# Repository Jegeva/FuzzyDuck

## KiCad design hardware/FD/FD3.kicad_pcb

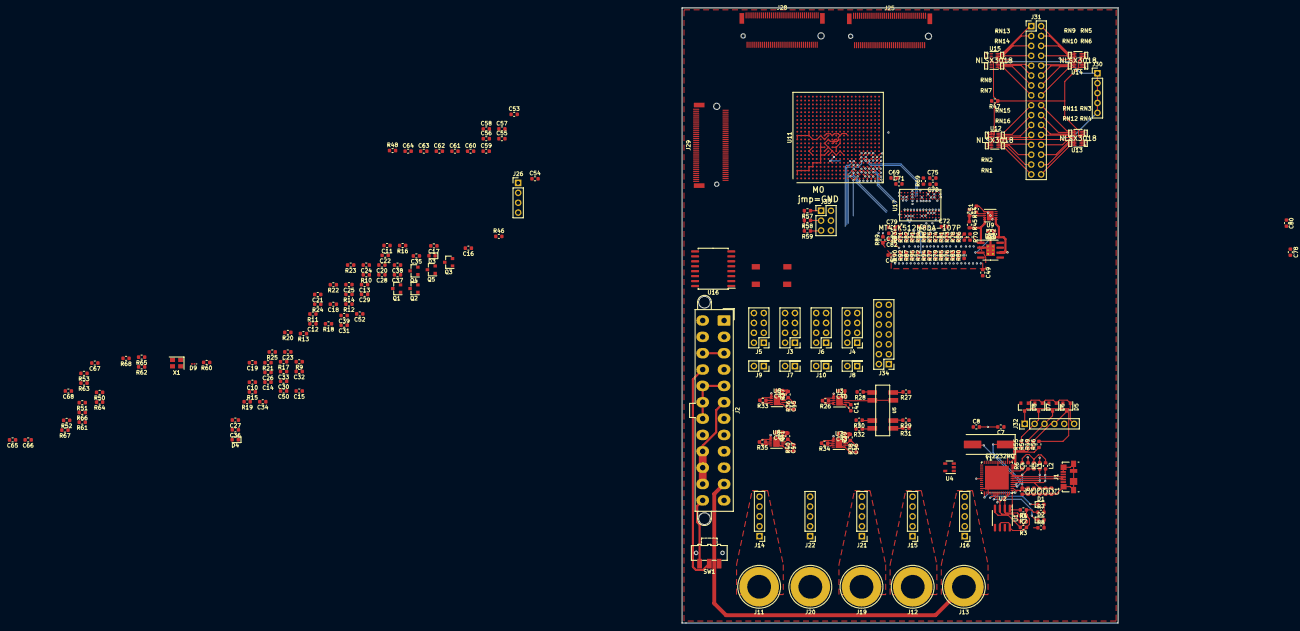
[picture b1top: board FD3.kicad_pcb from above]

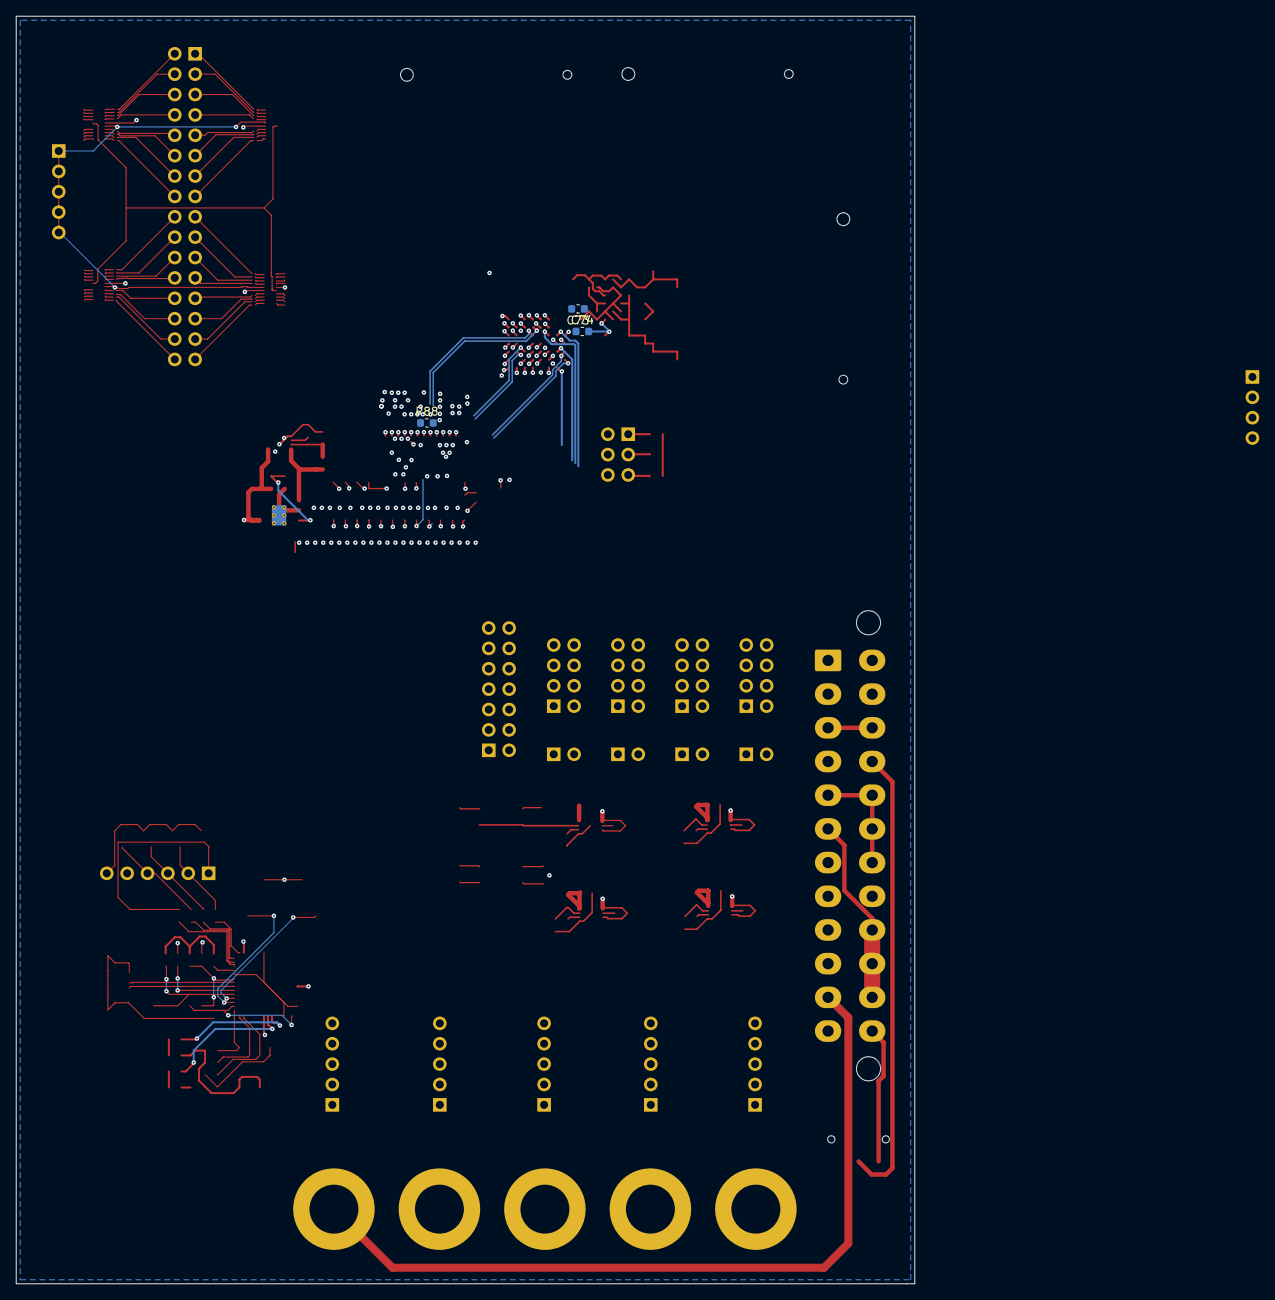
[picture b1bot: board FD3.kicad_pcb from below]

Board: 6 copper layers, 112.0 x 158.0 mm, 259 parts (3 on the bottom side), 413 nets.

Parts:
C1, C4: 4.7uF TA; C_0603_1608Metric
C2, C5, C66, C67, C68, C70, C71, C72, C73, C75, C79, C80, C82: 100nF; C_0603_1608Metric
C3, C6, C65, C69, C76, C77: 10nF; C_0603_1608Metric
C7, C8: 20pF; C_0603_1608Metric
C9, C10, C11, C12, C13, C14, C15, C16, C17, C18, C19, C20, C21: 4.7uF; C_0603_1608Metric
C22, C27, C40, C42, C43, C44, C48, C50: 100uF; C_0603_1608Metric
C23, C24, C25, C26, C28, C29, C30, C31, C32, C33, C34, C35: 0.47uF; C_0603_1608Metric
C36, C37, C38, C39: 0.1uF; C_0603_1608Metric
C41, C45, C46, C47, C51: 5.6nF; C_0603_1608Metric
C49, C52, C74, C78: 10uF; C_0603_1608Metric
C53, C54, C55, C56, C57, C58, C59, C60, C61, C62, C63, C64: 200nF; C_0603_1608Metric
D1, D2: LED_Small; LED_0603_1608Metric
D3, D4: LED; LED_0603_1608Metric
D5, D6, D7, D8: MMSZ4678-TPMSCT-ND‎; D_SOT-23_ANK
D9: LED_Small; LED_0201_0603Metric
J1: USB_B_Micro; USB_Micro-B_Molex_47346-0001
J2: ATX-24; Molex_Mini-Fit_Jr_5566-24A2_2x12_P4.20mm_Vertical
J3, J4, J5, J6: Conn_01x05; PinHeader_2x04_P2.54mm_Vertical
J7, J8, J9, J10: Conn_01x02_Male; PinHeader_2x01_P2.54mm_Vertical
J11, J12, J13, J19, J20: Conn_01x01_Male; Banana_Jack_1Pin
J14, J15, J16, J21, J22: Conn_01x05; PinHeader_1x05_P2.54mm_Vertical
J25, J28, J29: M.2_Socket_M; m.2
J26: Conn_01x06_Male; PinHeader_1x04_P2.54mm_Vertical
J30: Conn_01x05_Male; PinHeader_1x05_P2.54mm_Vertical
J31: Conn_02x16_Counter_Clockwise; PinHeader_2x16_P2.54mm_Vertical
J32: Conn_01x06_Male; PinHeader_1x06_P2.54mm_Vertical
J33: Conn_02x03_Counter_Clockwise; PinHeader_2x03_P2.54mm_Vertical
J34: Conn_02x07_Counter_Clockwise; PinHeader_2x07_P2.54mm_Vertical
L1, L2: 600R/100MHz; R_0603_1608Metric
Q1, Q2, Q3, Q4, Q5: DMG2301L; SOT-23
R1, R2, R3: 10k; R_0603_1608Metric
R4: 2.2k; R_0603_1608Metric
R5: 12k; R_0603_1608Metric
R6, R52, R53, R57, R58, R59: 1k; R_0603_1608Metric
R7, R8, R12, R17: 220; R_0603_1608Metric
R9, R10, R11, R13, R14, R15, R16, R18, R19, R20, R21, R22, R23, R24, R25, R26, R33, R34, R35, R42, R43: 47k; R_0603_1608Metric
R27, R36: 4.53k; R_0603_1608Metric
R28, R37: 1.13k; R_0603_1608Metric
R29, R38: 4.99k; R_0603_1608Metric
R30, R39: 2.49k; R_0603_1608Metric
R31, R40: 2.87k; R_0603_1608Metric
R32, R41: 3.57k; R_0603_1608Metric
R44, R47, R50, R51: 4.7k; R_0603_1608Metric
R45: 3.3k; R_0603_1608Metric
R46: 49.9; R_0603_1608Metric
R48, R49, R54, R55, R56, R60, R61: 100; R_0603_1608Metric
R62: 200; R_0603_1608Metric
R63, R64: 1.8k; R_0603_1608Metric
R65, R66, R67, R68: 50; R_0603_1608Metric
R69: 240; R_0603_1608Metric
R70, R93: 34; R_0603_1608Metric
R71, R72, R73, R74, R75, R76, R77, R78, R79, R80, R81, R82, R83, R84, R85, R86, R87, R89, R90, R91, R92, R94, R95, R96: 40; R_0603_1608Metric
R88: 68; R_0603_1608Metric
RN1, RN2, RN3, RN4, RN5, RN6, RN7, RN8, RN9, RN10, RN11, RN12, RN13, RN14, RN15, RN16: 1k x4; Resistor_Array_4x0503
SW1: SW_SPDT; SW_SPDT_CK-JS102011SAQN
SW2: SW_SPST; FSM4JSMATR
U1: 93CxxC; SOIC-8_3.9x4.9mm_P1.27mm
U2: FT2232HQ; VQFN-56-ftdi2232h-56q
U3, U6, U7, U8, U9: NCP59744-DFN10; DFN-10-1EP_3x3mm_P0.5mm_EP1.7x2.5mm
U4: 74LX1G00; SOT-23-5
U5: SWITCH_DP3T; JS203011SCQN
U10: AP2303; SOIC-8-1EP_3.9x4.9mm_P1.27mm_EP2.29x3mm_ThermalVias
U11: XC7A100T-FGG484; Xilinx_FGG484.p2d
U12, U13, U14, U15: NLSX3018; ON_Semiconductor-517AK-01-11_2006-O-MFG
U16: MT25Q128-8-ESF_SO16; SOIC-16W_7.5x10.3mm_P1.27mm
U17: MT41K512M8DA-107P; Micron-DA-0-0-0
X1: ASTMLPE-18-100.000MHZ-LJ-E-T; Oscillator_SMD_Abracon_ASE-4Pin_3.2x2.5mm
Y1: 12 MHz; Crystal_SMD_HC49-SD

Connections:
+3.3V: C27.2, J2.1 (+3.3V), J2.2 (+3.3V), J2.12 (+3.3V), J2.13 (+3.3V), J3.2, J4.2, J5.2, J6.2, J19.1, J21.1, J21.2, J21.3, J21.4, J21.5, J25.12 (3.3V), J28.12 (3.3V), J29.2 (3.3V), J29.4 (3.3V), J29.12 (3.3V), J29.14 (3.3V), J29.16 (3.3V), J29.18 (3.3V), J29.70 (3.3V), J29.72 (3.3V), J29.74 (3.3V), L1.1, L2.1, R1.1, R2.1, R3.1, R6.2, R7.1, R8.1, U1.6 (ORG), U1.8 (VCC), U2.16 (VCCIO), U2.36 (VCCIO), U2.44 (VREGIN), U2.50 (VCCIO)
+5V: C22.2, J2.4 (+5V), J2.6 (+5V), J2.21 (+5V), J2.22 (+5V), J2.23 (+5V), J12.1, J15.1, J15.2, J15.3, J15.4, J15.5, R26.2, R33.2, R34.2, R35.2, R43.1, U3.1 (IN), U3.2 (IN), U3.4 (BIAS), U4.5 (VCC), U6.1 (IN), U6.2 (IN), U6.4 (BIAS), U7.1 (IN), U7.2 (IN), U7.4 (BIAS), U8.1 (IN), U8.2 (IN), U8.4 (BIAS), U9.1 (IN), U9.2 (IN), U9.4 (BIAS), U10.6 (VCNTL)
+12V: J2.10 (+12V), J2.11 (+12V), J13.1, J16.1, J16.2, J16.3, J16.4, J16.5
-12V: J2.14 (-12V), J11.1, J14.1, J14.2, J14.3, J14.4, J14.5
/fgpa-logic/m0: J33.1, R57.1, U11.U11 (M0_0)
/fgpa-logic/m1: J33.3, R58.1, U11.U10 (M1_0)
/fgpa-logic/m2: J33.5, R59.1, U11.U9 (M2_0)
/fpga-io/b15_1_N: J25.47 (FDEXP_D1_N), U11.G13 (IO_L1N_T0_AD0N_15)
/fpga-io/b15_1_P: J25.49 (FDEXP_D1_P), U11.H13 (IO_L1P_T0_AD0P_15)
/fpga-io/b15_2_N: J25.41 (FDEXP_D2_N), U11.G16 (IO_L2N_T0_AD8N_15)
/fpga-io/b15_2_P: J25.43 (FDEXP_D2_P), U11.G15 (IO_L2P_T0_AD8P_15)
/fpga-io/b15_3_N: J25.53 (FDEXP_D3_N), U11.H14 (IO_L3N_T0_DQS_AD1N_15)
/fpga-io/b15_3_P: J25.55 (FDEXP_D3_P), U11.J14 (IO_L3P_T0_DQS_AD1P_15)
/fpga-io/b15_4_N: J25.52 (FDEXP_D4_N), U11.G18 (IO_L4N_T0_15)
/fpga-io/b15_4_P: J25.50 (FDEXP_D4_P), U11.G17 (IO_L4P_T0_15)
/fpga-io/b15_5_N: J25.37 (FDEXP_D5_N), U11.H15 (IO_L5N_T0_AD9N_15)
/fpga-io/b15_5_P: J25.54 (FDEXP_D5_P), U11.J15 (IO_L5P_T0_AD9P_15)
/fpga-io/b15_7_N: J25.29 (FDEXP_D7_N), U11.H22 (IO_L7N_T1_AD2N_15)
/fpga-io/b15_7_P: J25.31 (FDEXP_D7_P), U11.J22 (IO_L7P_T1_AD2P_15)
/fpga-io/b15_8_N: J25.23 (FDEXP_D8_N), U11.G20 (IO_L8N_T1_AD10N_15)
/fpga-io/b15_8_P: J25.25 (FDEXP_D8_P), U11.H20 (IO_L8P_T1_AD10P_15)
/fpga-io/b15_9_N: J25.17 (FDEXP_D9_N), U11.K22 (IO_L9N_T1_DQS_AD3N_15)
/fpga-io/b15_9_P: J25.19 (FDEXP_D9_P), U11.K21 (IO_L9P_T1_DQS_AD3P_15)
/fpga-io/b15_10_N: J25.11 (FDEXP_D10_N), U11.L21 (IO_L10N_T1_AD11N_15)
/fpga-io/b15_10_P: J25.13 (FDEXP_D10_P), U11.M21 (IO_L10P_T1_AD11P_15)
/fpga-io/b15_11_N: J25.5 (FDEXP_D11_N), U11.J21 (IO_L11N_T1_SRCC_15)
/fpga-io/b15_11_P: J25.7 (FDEXP_D11_P), U11.J20 (IO_L11P_T1_SRCC_15)
/fpga-io/b15_12_N: J25.18 (FDEXP_D12_N), U11.H19 (IO_L12N_T1_MRCC_15)
/fpga-io/b15_12_P: J25.16 (FDEXP_D12_P), U11.J19 (IO_L12P_T1_MRCC_15)
/fpga-io/b15_13_N: J25.4 (FDEXP_D13_N), U11.K19 (IO_L13N_T2_MRCC_15)
/fpga-io/b15_13_P: J25.2 (FDEXP_D13_P), U11.K18 (IO_L13P_T2_MRCC_15)
/fpga-io/b15_14_N: J25.74 (FDEXP_D14_N), U11.L20 (IO_L14N_T2_SRCC_15)
/fpga-io/b15_14_P: J25.72 (FDEXP_D14_P), U11.L19 (IO_L14P_T2_SRCC_15)
/fpga-io/b15_15_N: J25.3 (FDEXP_D15_N), U11.M22 (IO_L15N_T2_DQS_ADV_B_15)
/fpga-io/b15_15_P: J25.1 (FDEXP_D15_P), U11.N22 (IO_L15P_T2_DQS_15)
/fpga-io/b15_16_N: J25.15 (FDEXP_D16_N), U11.L18 (IO_L16N_T2_A27_15)
/fpga-io/b15_16_P: J25.9 (FDEXP_D16_P), U11.M18 (IO_L16P_T2_A28_15)
/fpga-io/b15_17_N: J25.27 (FDEXP_D17_N), U11.N19 (IO_L17N_T2_A25_15)
/fpga-io/b15_17_P: J25.21 (FDEXP_D17_P), U11.N18 (IO_L17P_T2_A26_15)
/fpga-io/b15_18_N: J25.39 (FDEXP_D18_N), U11.M20 (IO_L18N_T2_A23_15)
/fpga-io/b15_18_P: J25.33 (FDEXP_D18_P), U11.N20 (IO_L18P_T2_A24_15)
/fpga-io/b15_20_N: J25.57 (FDEXP_D20_N), U11.L13 (IO_L20N_T3_A19_15)
/fpga-io/b15_20_P: J25.51 (FDEXP_D20_p), U11.M13 (IO_L20P_T3_A20_15)
/fpga-io/b15_21_N: J25.73 (FDEXP_D21_N), U11.J17 (IO_L21N_T3_DQS_A18_15)
/fpga-io/b15_21_P: J25.71 (FDEXP_D21_P), U11.K17 (IO_L21P_T3_DQS_15)
/fpga-io/b15_22_N: J25.69 (FDEXP_D22_N), U11.L15 (IO_L22N_T3_A16_15)
/fpga-io/b15_22_P: J25.68 (FDEXP_D22_P), U11.L14 (IO_L22P_T3_A17_15)
/fpga-io/b15_23_N: J25.10 (FDEXP_D23_N), U11.K16 (IO_L23N_T3_FWE_B_15)
/fpga-io/b15_23_P: J25.75 (FDEXP_D23_P), U11.L16 (IO_L23P_T3_FOE_B_15)
/fpga-io/b16_1_N: J28.47 (FDEXP_D1_N), U11.F14 (IO_L1N_T0_16)
/fpga-io/b16_1_P: J28.49 (FDEXP_D1_P), U11.F13 (IO_L1P_T0_16)
/fpga-io/b16_2_N: J28.41 (FDEXP_D2_N), U11.E17 (IO_L2N_T0_16)
/fpga-io/b16_2_P: J28.43 (FDEXP_D2_P), U11.F16 (IO_L2P_T0_16)
/fpga-io/b16_3_N: J28.53 (FDEXP_D3_N), U11.C15 (IO_L3N_T0_DQS_16)
/fpga-io/b16_3_P: J28.55 (FDEXP_D3_P), U11.C14 (IO_L3P_T0_DQS_16)
/fpga-io/b16_4_N: J28.52 (FDEXP_D4_N), U11.E14 (IO_L4N_T0_16)
/fpga-io/b16_4_P: J28.50 (FDEXP_D4_P), U11.E13 (IO_L4P_T0_16)
/fpga-io/b16_5_N: J28.37 (FDEXP_D5_N), U11.D16 (IO_L5N_T0_16)
/fpga-io/b16_5_P: J28.54 (FDEXP_D5_P), U11.E16 (IO_L5P_T0_16)
/fpga-io/b16_7_N: J28.29 (FDEXP_D7_N), U11.B16 (IO_L7N_T1_16)
/fpga-io/b16_7_P: J28.31 (FDEXP_D7_P), U11.B15 (IO_L7P_T1_16)
/fpga-io/b16_8_N: J28.23 (FDEXP_D8_N), U11.B13 (IO_L8N_T1_16)
/fpga-io/b16_8_P: J28.25 (FDEXP_D8_P), U11.C13 (IO_L8P_T1_16)
/fpga-io/b16_9_N: J28.17 (FDEXP_D9_N), U11.A16 (IO_L9N_T1_DQS_16)
/fpga-io/b16_9_P: J28.19 (FDEXP_D9_P), U11.A15 (IO_L9P_T1_DQS_16)
/fpga-io/b16_10_N: J28.11 (FDEXP_D10_N), U11.A14 (IO_L10N_T1_16)
/fpga-io/b16_10_P: J28.13 (FDEXP_D10_P), U11.A13 (IO_L10P_T1_16)
/fpga-io/b16_11_N: J28.5 (FDEXP_D11_N), U11.B18 (IO_L11N_T1_SRCC_16)
/fpga-io/b16_11_P: J28.7 (FDEXP_D11_P), U11.B17 (IO_L11P_T1_SRCC_16)
/fpga-io/b16_12_N: J28.18 (FDEXP_D12_N), U11.C17 (IO_L12N_T1_MRCC_16)
/fpga-io/b16_12_P: J28.16 (FDEXP_D12_P), U11.D17 (IO_L12P_T1_MRCC_16)
/fpga-io/b16_13_N: J28.4 (FDEXP_D13_N), U11.C19 (IO_L13N_T2_MRCC_16)
/fpga-io/b16_13_P: J28.2 (FDEXP_D13_P), U11.C18 (IO_L13P_T2_MRCC_16)
/fpga-io/b16_14_N: J28.74 (FDEXP_D14_N), U11.D19 (IO_L14N_T2_SRCC_16)
/fpga-io/b16_14_P: J28.72 (FDEXP_D14_P), U11.E19 (IO_L14P_T2_SRCC_16)
/fpga-io/b16_15_N: J28.3 (FDEXP_D15_N), U11.E18 (IO_L15N_T2_DQS_16)
/fpga-io/b16_15_P: J28.1 (FDEXP_D15_P), U11.F18 (IO_L15P_T2_DQS_16)
/fpga-io/b16_16_N: J28.15 (FDEXP_D16_N), U11.A20 (IO_L16N_T2_16)
/fpga-io/b16_16_P: J28.9 (FDEXP_D16_P), U11.B20 (IO_L16P_T2_16)
/fpga-io/b16_17_N: J28.27 (FDEXP_D17_N), U11.A19 (IO_L17N_T2_16)
/fpga-io/b16_17_P: J28.21 (FDEXP_D17_P), U11.A18 (IO_L17P_T2_16)
/fpga-io/b16_18_N: J28.39 (FDEXP_D18_N), U11.F20 (IO_L18N_T2_16)
/fpga-io/b16_18_P: J28.33 (FDEXP_D18_P), U11.F19 (IO_L18P_T2_16)
/fpga-io/b16_20_N: J28.57 (FDEXP_D20_N), U11.B22 (IO_L20N_T3_16)
/fpga-io/b16_20_P: J28.51 (FDEXP_D20_p), U11.C22 (IO_L20P_T3_16)
/fpga-io/b16_21_N: J28.73 (FDEXP_D21_N), U11.A21 (IO_L21N_T3_DQS_16)
/fpga-io/b16_21_P: J28.71 (FDEXP_D21_P), U11.B21 (IO_L21P_T3_DQS_16)
/fpga-io/b16_22_N: J28.69 (FDEXP_D22_N), U11.D22 (IO_L22N_T3_16)
/fpga-io/b16_22_P: J28.68 (FDEXP_D22_P), U11.E22 (IO_L22P_T3_16)
/fpga-io/b16_23_N: J28.10 (FDEXP_D23_N), U11.D21 (IO_L23N_T3_16)
/fpga-io/b16_23_P: J28.75 (FDEXP_D23_P), U11.E21 (IO_L23P_T3_16)
/usb-interface/D+: J1.3 (D+), U2.8 (DP)
/usb-interface/D-: J1.2 (D-), U2.7 (DM)
ATX_POWEROK: J2.8 (PWR_OK), R12.2, U6.5 (EN)
DDR_A0: R72.2, U11.AA6 (IO_L18N_T2_34), U17.K3 (A0)
DDR_A1: R73.2, U11.AA4 (IO_L11N_T1_SRCC_34), U17.L7 (A1)
DDR_A2: R74.2, U11.AB7 (IO_L20P_T3_34), U17.L3 (A2)
DDR_A3: R75.2, U11.U7 (IO_25_34), U17.K2 (A3)
DDR_A4: R76.2, U11.AA5 (IO_L10P_T1_34), U17.L8 (A4)
DDR_A5: R77.2, U11.V7 (IO_L19P_T3_34), U17.L2 (A5)
DDR_A6: R78.2, U11.AB5 (IO_L10N_T1_34), U17.M8 (A6)
DDR_A7: R79.2, U11.W7 (IO_L19N_T3_VREF_34), U17.M2 (A7)
DDR_A8: R80.2, U11.T4 (IO_L13N_T2_MRCC_34), U17.N8 (A8)
DDR_A9: R81.2, U11.Y6 (IO_L18P_T2_34), U17.M3 (A9)
DDR_A10: R82.2, U11.AA1 (IO_L7P_T1_34), U17.H7 (A10/AP)
DDR_A11: R83.2, U11.R4 (IO_L13P_T2_MRCC_34), U17.M7 (A11)
DDR_A12: R84.2, U11.AB2 (IO_L8N_T1_34), U17.K7 (A12/~BC~)
DDR_A13: R85.2, U11.Y7 (IO_L23N_T3_34), U17.N3 (A13)
DDR_A14: R86.2, U11.AB6 (IO_L20N_T3_34), U17.N7 (A14)
DDR_A15: R87.2, U11.AB1 (IO_L7N_T1_34), U17.J7 (A15)
DDR_BA0: R94.2, U11.AB3 (IO_L8P_T1_34), U17.J2 (BA0)
DDR_BA1: R95.2, U11.W4 (IO_L12N_T1_MRCC_34), U17.K8 (BA1)
DDR_BA2: R96.2, U11.V4 (IO_L12P_T1_MRCC_34), U17.J3 (BA2)
DDR_CKE: R90.2, U11.AB8 (IO_L22N_T3_34), U17.G9 (CKE)
DDR_CK_N: R88.1, U11.W5 (IO_L15N_T2_DQS_34), U17.G7 (~CK~)
DDR_CK_P: R88.2, U11.W6 (IO_L15P_T2_DQS_34), U17.F7 (CK)
DDR_DQ0: U11.V2 (IO_L2N_T0_34), U17.B3 (DQ0)
DDR_DQ1: U11.Y1 (IO_L5N_T0_34), U17.C7 (DQ1)
DDR_DQ2: U11.U1 (IO_L1N_T0_34), U17.C2 (DQ2)
DDR_DQ3: U11.Y2 (IO_L4N_T0_34), U17.C8 (DQ3)
DDR_DQ4: U11.U3 (IO_L6P_T0_34), U17.E3 (DQ4)
DDR_DQ5: U11.W2 (IO_L4P_T0_34), U17.E8 (DQ5)
DDR_DQ6: U11.U2 (IO_L2P_T0_34), U17.D2 (DQ6)
DDR_DQ7: U11.W1 (IO_L5P_T0_34), U17.E7 (DQ7)
DDR_DQS_N: U11.R2 (IO_L3N_T0_DQS_34), U17.D3 (~DQS~)
DDR_DQS_P: U11.R3 (IO_L3P_T0_DQS_34), U17.C3 (DQS)
DDR_NCAS: R92.2, U11.T3 (IO_0_34), U17.G3 (~CAS~)
DDR_NCS: R91.2, U11.T5 (IO_L14P_T2_SRCC_34), U17.H2 (~CS~)
DDR_NRAS: R71.2, U11.T1 (IO_L1P_T0_34), U17.F3 (~RAS~)
DDR_NRST: R70.1, U11.AA8 (IO_L22P_T3_34), U17.N2 (~RESET~)
DDR_NWE: R93.2, U11.U5 (IO_L14N_T2_SRCC_34), U17.H3 (~WE~)
DDR_ODT: R89.2, U11.V3 (IO_L6N_T0_VREF_34), U17.G1 (ODT)
DDR_TDQS_N: U11.AA3 (IO_L9N_T1_DQS_34), U17.A7 (NF/~TDQS~)
DDR_TDQS_P: U11.Y3 (IO_L9P_T1_DQS_34), U17.B7 (DM/TDQS)
FLASH_CONFIG_CLK: J34.5, R46.1, R60.1, U11.L12 (CCLK_0)
FLASH_CONFIG_CS: J34.6, U11.T19 (IO_L6P_T0_FCS_B_14)
FLASH_CONFIG_IO_0: J34.1, U11.P22 (IO_L1P_T0_D00_MOSI_14)
FLASH_CONFIG_IO_1: J34.2, U11.R22 (IO_L1N_T0_D01_DIN_14)
FLASH_CONFIG_IO_2: J34.3, U11.P21 (IO_L2P_T0_D02_14)
FLASH_CONFIG_IO_3: J34.4, U11.R21 (IO_L2N_T0_D03_14)
FPGA-CLK-100: U11.W19 (IO_L12P_T1_MRCC_14), X1.3 (OUT)
FPGA_SER_RX: U2.33 (BDBUS1), U11.N5 (IO_L24N_T3_35)
FPGA_SER_TX: U2.32 (BDBUS0), U11.P6 (IO_L24P_T3_35)
FPGA_TDCLK: R56.1, U2.12 (ADBUS0)
FPGA_TDI: R49.1, U2.13 (ADBUS1)
FPGA_TDO: R54.1, U2.14 (ADBUS2)
FPGA_TMS: R55.1, U2.15 (ADBUS3)
GND: C1.2, C2.2, C3.2, C4.2, C5.2, C6.2, C7.2, C8.2, C9.2, C10.2, C11.2, C12.2, C13.2, C14.2, C15.2, C16.2, C17.2, C18.2, C19.2, C20.2, C21.2, C22.1, C23.2, C24.2, C25.2, C26.2, C27.1, C28.2, C29.2, C30.2, C31.2, C32.2, C33.2, C34.2, C35.2, C36.2, C37.2, C38.2, C39.2, C40.2, C41.2, C42.2, C43.2, C44.2, C45.2, C46.2, C47.2, C48.2, C49.2, C50.2, C51.2, C52.2, C65.2, C66.2, C67.2, C68.1, C69.2, C70.2, C71.2, C72.2, C73.2, C74.2, C75.2, C76.2, C78.2, C79.1, C80.2, C82.2, D3.1 (K), D4.1 (K), D5.2 (A), D6.2 (A), D7.2 (A), D8.2 (A), D9.1 (K), J1.5 (GND), J1.6 (Shield), J2.3 (GND), J2.5 (GND), J2.7 (GND), J2.15 (GND), J2.17 (GND), J2.18 (GND), J2.19 (GND), J2.24 (GND), J20.1, J22.1, J22.2, J22.3, J22.4, J22.5, J25.14 (GND), J28.14 (GND), J29.1 (GND), J29.3 (GND), J29.9 (GND), J29.15 (GND), J29.21 (GND), J29.27 (GND), J29.33 (GND), J29.39 (GND), J29.45 (GND), J29.51 (GND), J29.57 (GND), J29.71 (GND), J29.73 (GND), J29.75 (GND), J32.6, J33.2, J33.4, J33.6, J34.7, R5.2, R9.1, R10.2, R13.1, R14.1, R15.1, R16.1, R18.2, R20.2, R22.2, R24.2, R27.1, R29.1, R31.1, R36.1, R38.1, R40.1, R42.2, R44.1, R47.2, R52.1, R53.1, R69.2, SW1.3 (C), SW2.2 (B), U1.5 (GND), U2.10 (TEST), U2.21 (GND), U2.41 (GND), U2.45 (GND), U3.6 (GND), U4.3 (GND), U6.6 (GND), U7.6 (GND), U8.6 (GND), U9.6 (GND), U10.2 (GND), U10.9 (GND/TPAD), U11.A2 (GND), U11.A3 (GND), U11.A5 (GND), U11.A7 (GND), U11.A9 (GND), U11.A11 (GND), U11.A12 (GND), U11.A22 (GND), U11.AA2 (GND), U11.AA12 (GND), U11.AA22 (GND), U11.AB9 (GND), U11.AB19 (GND), U11.B3 (GND), U11.B12 (GND), U11.B19 (GND), U11.C3 (GND), U11.C6 (GND), U11.C10 (GND), U11.C12 (GND), U11.C16 (GND), U11.D3 (GND), U11.D4 (GND), U11.D8 (GND), U11.D12 (GND), U11.D13 (GND), U11.E4 (GND), U11.E5 (GND), U11.E7 (GND), U11.E9 (GND), U11.E11 (GND), U11.E20 (GND), U11.F5 (GND), U11.F11 (GND), U11.F17 (GND), U11.G5 (GND), U11.G6 (GND), U11.G7 (GND), U11.G8 (GND), U11.G9 (GND), U11.G10 (GND), U11.G12 (GND), U11.G14 (GND), U11.H1 (GND), U11.H7 (GND), U11.H9 (GND), U11.H11 (GND), U11.H21 (GND), U11.J8 (GND), U11.J10 (GND), U11.J12 (GND), U11.J18 (GND), U11.K5 (GND), U11.K7 (GND), U11.K9 (GNDADC_0), U11.K11 (GND), U11.K15 (GND), U11.L2 (GND), U11.L8 (GND), U11.L9 (VREFN_0), U11.L22 (GND), U11.M7 (GND), U11.M10 (VREFP_0), U11.M11 (GND), U11.M19 (GND), U11.N6 (GND), U11.N8 (GND), U11.N16 (GND), U11.P3 (GND), U11.P7 (GND), U11.P9 (GND), U11.P11 (GND), U11.P13 (GND), U11.R8 (GND), U11.R10 (GND), U11.R12 (GND), U11.R20 (GND), U11.T7 (GND), U11.T9 (GND), U11.T11 (GND), U11.T17 (GND), U11.U4 (GND), U11.U8 (CFGBVS_0), U11.U14 (GND), U11.V1 (GND), U11.V11 (GND), U11.V21 (GND), U11.W8 (GND), U11.W18 (GND), U11.Y5 (GND), U11.Y15 (GND), U12.15 (GND), U13.15 (GND), U14.15 (GND), U15.15 (GND), U17.A1 (VSS), U17.A8 (VSS), U17.B1 (VSS), U17.B2 (VSSQ), U17.B8 (VSSQ), U17.C9 (VSSQ), U17.D1 (VSSQ), U17.D8 (VSS), U17.D9 (VSSQ), U17.F2 (VSS), U17.F8 (VSS), U17.J1 (VSS), U17.J9 (VSS), U17.L1 (VSS), U17.L9 (VSS), U17.N1 (VSS), U17.N9 (VSS), X1.2 (GND)
MGTPCLK0_N: C63.2, J29.53 (REFCLKn)
MGTPCLK0_P: C57.2, J29.55 (REFCLKp)
MGTPRX0_N: J29.47 (PETn0/SATA-A-), U11.A8 (MGTPRXN0_216)
MGTPRX0_P: J29.49 (PETp0/SATA-A+), U11.B8 (MGTPRXP0_216)
MGTPRX1_N: J29.35 (PETn1), U11.C11 (MGTPRXN1_216)
MGTPRX1_P: J29.37 (PETp1), U11.D11 (MGTPRXP1_216)
MGTPRX2_N: J29.23 (PETn2), U11.A10 (MGTPRXN2_216)
MGTPRX2_P: J29.25 (PETp2), U11.B10 (MGTPRXP2_216)
MGTPRX3_N: J29.11 (PETn3), U11.C9 (MGTPRXN3_216)
MGTPRX3_P: J29.13 (PETp3), U11.D9 (MGTPRXP3_216)
MGTPTX0_N: C59.2, J29.41 (PERn0/SATA-B+)
MGTPTX0_P: C53.2, J29.43 (PERp0/SATA-B-)
MGTPTX1_N: C60.2, J29.29 (PERn1)
MGTPTX1_P: C54.2, J29.31 (PERp1)
MGTPTX2_N: C61.2, J29.17 (PERn2)
MGTPTX2_P: C55.2, J29.19 (PERp2)
MGTPTX3_N: C62.2, J29.5 (PERn3)
MGTPTX3_P: C56.2, J29.7 (PERp3)
unnamed: C1.1, C2.1, C3.1, L2.2, U2.5 (VPHY)
unnamed: C4.1, C5.1, C6.1, L1.2, U2.9 (VPLL)
unnamed: C7.1, U2.3 (OSCI), Y1.1
unnamed: C8.1, U2.4 (OSCO), Y1.2
unnamed: C9.1, U2.2 (VCORE), U2.31 (VCORE), U2.43 (VREGOUT)
unnamed: C41.1, U3.7 (SS)
unnamed: C45.1, U6.7 (SS)
unnamed: C46.1, U7.7 (SS)
unnamed: C47.1, U8.7 (SS)
unnamed: C51.1, U9.7 (SS)
unnamed: C53.1, U11.B4 (MGTPTXP0_216)
unnamed: C54.1, U11.D5 (MGTPTXP1_216)
unnamed: C55.1, U11.B6 (MGTPTXP2_216)
unnamed: C56.1, U11.D7 (MGTPTXP3_216)
unnamed: C57.1, U11.F6 (MGTREFCLK0P_216)
unnamed: C58.1, U11.F10 (MGTREFCLK1P_216)
unnamed: C59.1, U11.A4 (MGTPTXN0_216)
unnamed: C60.1, U11.C5 (MGTPTXN1_216)
unnamed: C61.1, U11.A6 (MGTPTXN2_216)
unnamed: C62.1, U11.C7 (MGTPTXN3_216)
unnamed: C63.1, U11.E6 (MGTREFCLK0N_216)
unnamed: C64.1, U11.E10 (MGTREFCLK1N_216)
unnamed: D1.1 (K), U2.48 (BCBUS3)
unnamed: D1.2 (A), R7.2
unnamed: D2.1 (K), U2.49 (BCBUS4)
unnamed: D2.2 (A), R8.2
unnamed: D3.2 (A), R12.1
unnamed: D4.2 (A), R17.1
unnamed: D5.1 (K), J32.4, R49.2, U11.R13 (TDI_0)
unnamed: D6.1 (K), J32.3, R54.2, U11.U13 (TDO_0)
unnamed: D7.1 (K), J32.2, R55.2, U11.T13 (TMS_0)
unnamed: D8.1 (K), J32.1, R56.2, U11.V12 (TCK_0)
unnamed: D9.2 (A), R61.1
unnamed: J2.9 (+5VSB), R17.2
unnamed: J2.16 (PS_ON#), SW1.2 (B)
unnamed: J3.1, J3.3, J3.5, J3.7, Q2.2 (S)
unnamed: J4.1, J4.3, J4.5, J4.7, Q3.2 (S)
unnamed: J5.1, J5.3, J5.5, J5.7, Q4.2 (S)
unnamed: J6.1, J6.3, J6.5, J6.7, Q5.2 (S)
unnamed: J7.2, R18.1, R19.2
unnamed: J8.2, R20.1, R21.2
unnamed: J9.2, R22.1, R23.2
unnamed: J10.2, R24.1, R25.2
unnamed: J25.35 (FDEXP_GPIO0), U11.H17 (IO_L6P_T0_15)
unnamed: J25.38 (FDEXP_GPIO1), U11.M17 (IO_25_15)
unnamed: J25.45 (FDEXP_GPIO3), U11.K13 (IO_L19P_T3_A22_15)
unnamed: J25.70 (FDEXP_GPIO2), U11.J16 (IO_0_15)
unnamed: J28.35 (FDEXP_GPIO0), U11.D14 (IO_L6P_T0_16)
unnamed: J28.38 (FDEXP_GPIO1), U11.F21 (IO_25_16)
unnamed: J28.45 (FDEXP_GPIO3), U11.D20 (IO_L19P_T3_16)
unnamed: J28.70 (FDEXP_GPIO2), U11.F15 (IO_0_16)
unnamed: J30.1, J30.2, J30.3, J30.4, J30.5, U12.16 (VCC), U13.16 (VCC), U14.16 (VCC), U15.16 (VCC)
unnamed: J31.1, RN13.8 (R1.2)
unnamed: J31.2, RN9.1 (R1.1)
unnamed: J31.3, RN13.7 (R2.2)
unnamed: J31.4, RN9.2 (R2.1)
unnamed: J31.5, RN13.6 (R3.2)
unnamed: J31.6, RN9.3 (R3.1)
unnamed: J31.7, RN13.5 (R4.2)
unnamed: J31.8, RN9.4 (R4.1)
unnamed: J31.9, RN14.8 (R1.2)
unnamed: J31.10, RN10.1 (R1.1)
unnamed: J31.11, RN14.7 (R2.2)
unnamed: J31.12, RN10.2 (R2.1)
unnamed: J31.13, RN14.6 (R3.2)
unnamed: J31.14, RN10.3 (R3.1)
unnamed: J31.15, RN14.5 (R4.2)
unnamed: J31.16, RN10.4 (R4.1)
unnamed: J31.17, RN15.8 (R1.2)
unnamed: J31.18, RN11.1 (R1.1)
unnamed: J31.19, RN15.7 (R2.2)
unnamed: J31.20, RN11.2 (R2.1)
unnamed: J31.21, RN15.6 (R3.2)
unnamed: J31.22, RN11.3 (R3.1)
unnamed: J31.23, RN15.5 (R4.2)
unnamed: J31.24, RN11.4 (R4.1)
unnamed: J31.25, RN16.8 (R1.2)
unnamed: J31.26, RN12.1 (R1.1)
unnamed: J31.27, RN16.7 (R2.2)
unnamed: J31.28, RN12.2 (R2.1)
unnamed: J31.29, RN16.6 (R3.2)
unnamed: J31.30, RN12.3 (R3.1)
unnamed: J31.31, RN16.5 (R4.2)
unnamed: J31.32, RN12.4 (R4.1)
unnamed: J34.8, U16.10 (GND)
unnamed: J34.9, U16.7 (~CE)
unnamed: J34.10, U16.16 (SCK)
unnamed: J34.11, R63.2, R67.2
unnamed: J34.12, R64.2, R66.2
unnamed: J34.13, R68.1
unnamed: J34.14, R65.2
unnamed: R1.2, U1.1 (CS), U2.1 (EECS)
unnamed: R2.2, U1.2 (SCLK), U2.56 (EECLK)
unnamed: R3.2, R4.2, U1.4 (DO)
unnamed: R4.1, U1.3 (DI), U2.55 (EEDATA)
unnamed: R5.1, U2.6 (REF)
unnamed: R6.1, U2.11 (~RESET)
unnamed: R26.1, U3.3 (PG)
unnamed: R27.2, U5.4 (P1T1)
unnamed: R28.1, U5.8 (P2T1)
unnamed: R29.2, U5.2 (P1T2)
unnamed: R30.1, U5.6 (P2T2)
unnamed: R31.2, U5.1 (P1T3)
unnamed: R32.1, U5.5 (P2T3)
unnamed: R34.1, U4.2 (B), U7.3 (PG)
unnamed: R35.1, U4.1 (A), U8.3 (PG)
unnamed: R36.2, R37.1, U6.8 (FB)
unnamed: R38.2, R39.1, U7.8 (FB)
unnamed: R40.2, R41.1, U8.8 (FB)
unnamed: R42.1, R43.2, U9.3 (PG), U10.3 (VREFEN)
unnamed: R44.2, R45.1, U9.8 (FB)
unnamed: R46.2, U11.V22 (IO_L3N_T0_DQS_EMCCLK_14)
unnamed: R48.2, U11.F8 (MGTRREF_216)
unnamed: R50.2, U11.U12 (INIT_B_0)
unnamed: R51.2, SW2.1 (A), U11.N12 (PROGRAM_B_0)
unnamed: R52.2, U11.L10 (VP_0)
unnamed: R53.2, U11.M9 (VN_0)
unnamed: R61.2, R62.1, U11.G11 (DONE_0)
unnamed: R65.1, U16.15 (SI/IO0)
unnamed: R66.1, U16.9 (~WP~/IO2)
unnamed: R67.1, U16.1 (~HOLD~/IO3)
unnamed: R68.2, U16.8 (SO/IO1)
unnamed: R69.1, U17.H8 (ZQ)
unnamed: RN1.1 (R1.1), U12.10 (A8)
unnamed: RN1.2 (R2.1), U12.9 (A7)
unnamed: RN1.3 (R3.1), U12.8 (A6)
unnamed: RN1.4 (R4.1), U12.7 (A5)
unnamed: RN1.5 (R4.2), U11.U20 (IO_L11P_T1_SRCC_14)
unnamed: RN1.6 (R3.2), U11.AB22 (IO_L10N_T1_D15_14)
unnamed: RN1.7 (R2.2), U11.AB21 (IO_L10P_T1_D14_14)
unnamed: RN1.8 (R1.2), U11.Y22 (IO_L9N_T1_DQS_D13_14)
unnamed: RN2.1 (R1.1), U12.4 (A4)
unnamed: RN2.2 (R2.1), U12.3 (A3)
unnamed: RN2.3 (R3.1), U12.2 (A2)
unnamed: RN2.4 (R4.1), U12.1 (A1)
unnamed: RN2.5 (R4.2), U11.Y19 (IO_L13N_T2_MRCC_14)
unnamed: RN2.6 (R3.2), U11.Y18 (IO_L13P_T2_MRCC_14)
unnamed: RN2.7 (R2.2), U11.W20 (IO_L12N_T1_MRCC_14)
unnamed: RN2.8 (R1.2), U11.V20 (IO_L11N_T1_SRCC_14)
unnamed: RN3.1 (R1.1), U13.10 (A8)
unnamed: RN3.2 (R2.1), U13.9 (A7)
unnamed: RN3.3 (R3.1), U13.8 (A6)
unnamed: RN3.4 (R4.1), U13.7 (A5)
unnamed: RN3.5 (R4.2), U11.AB20 (IO_L15N_T2_DQS_DOUT_CSO_B_14)
unnamed: RN3.6 (R3.2), U11.AA19 (IO_L15P_T2_DQS_RDWR_B_14)
unnamed: RN3.7 (R2.2), U11.V19 (IO_L14N_T2_SRCC_14)
unnamed: RN3.8 (R1.2), U11.V18 (IO_L14P_T2_SRCC_14)
unnamed: RN4.1 (R1.1), U13.4 (A4)
unnamed: RN4.2 (R2.1), U13.3 (A3)
unnamed: RN4.3 (R3.1), U13.2 (A2)
unnamed: RN4.4 (R4.1), U13.1 (A1)
unnamed: RN4.5 (R4.2), U11.AB18 (IO_L17N_T2_A13_D29_14)
unnamed: RN4.6 (R3.2), U11.AA18 (IO_L17P_T2_A14_D30_14)
unnamed: RN4.7 (R2.2), U11.W17 (IO_L16N_T2_A15_D31_14)
unnamed: RN4.8 (R1.2), U11.V17 (IO_L16P_T2_CSI_B_14)
unnamed: RN5.1 (R1.1), U14.10 (A8)
unnamed: RN5.2 (R2.1), U14.9 (A7)
unnamed: RN5.3 (R3.1), U14.8 (A6)
unnamed: RN5.4 (R4.1), U14.7 (A5)
unnamed: RN5.5 (R4.2), U11.R18 (IO_L20P_T3_A08_D24_14)
unnamed: RN5.6 (R3.2), U11.P14 (IO_L19P_T3_A10_D26_14)
unnamed: RN5.7 (R2.2), U11.U18 (IO_L18N_T2_A11_D27_14)
unnamed: RN5.8 (R1.2), U11.U17 (IO_L18P_T2_A12_D28_14)
unnamed: RN6.1 (R1.1), U14.4 (A4)
unnamed: RN6.2 (R2.1), U14.3 (A3)
unnamed: RN6.3 (R3.1), U14.2 (A2)
unnamed: RN6.4 (R4.1), U14.1 (A1)
unnamed: RN6.5 (R4.2), U11.P15 (IO_L22P_T3_A05_D21_14)
unnamed: RN6.6 (R3.2), U11.P17 (IO_L21N_T3_DQS_A06_D22_14)
unnamed: RN6.7 (R2.2), U11.N17 (IO_L21P_T3_DQS_14)
unnamed: RN6.8 (R1.2), U11.T18 (IO_L20N_T3_A07_D23_14)
unnamed: RN7.1 (R1.1), U15.10 (A8)
unnamed: RN7.2 (R2.1), U15.9 (A7)
unnamed: RN7.3 (R3.1), U15.8 (A6)
unnamed: RN7.4 (R4.1), U15.7 (A5)
unnamed: RN7.5 (R4.2), U11.W21 (IO_L7P_T1_D09_14)
unnamed: RN7.6 (R3.2), U11.R19 (IO_L5N_T0_D07_14)
unnamed: RN7.7 (R2.2), U11.P19 (IO_L5P_T0_D06_14)
unnamed: RN7.8 (R1.2), U11.U21 (IO_L4N_T0_D05_14)
unnamed: RN8.1 (R1.1), U15.4 (A4)
unnamed: RN8.2 (R2.1), U15.3 (A3)
unnamed: RN8.3 (R3.1), U15.2 (A2)
unnamed: RN8.4 (R4.1), U15.1 (A1)
unnamed: RN8.5 (R4.2), U11.Y21 (IO_L9P_T1_DQS_14)
unnamed: RN8.6 (R3.2), U11.AA21 (IO_L8N_T1_D12_14)
unnamed: RN8.7 (R2.2), U11.AA20 (IO_L8P_T1_D11_14)
unnamed: RN8.8 (R1.2), U11.W22 (IO_L7N_T1_D10_14)
unnamed: RN9.5 (R4.2), U14.14 (B5)
unnamed: RN9.6 (R3.2), U14.13 (B6)
unnamed: RN9.7 (R2.2), U14.12 (B7)
unnamed: RN9.8 (R1.2), U14.11 (B8)
unnamed: RN10.5 (R4.2), U14.20 (B1)
unnamed: RN10.6 (R3.2), U14.19 (B2)
unnamed: RN10.7 (R2.2), U14.18 (B3)
unnamed: RN10.8 (R1.2), U14.17 (B4)
unnamed: RN11.5 (R4.2), U13.14 (B5)
unnamed: RN11.6 (R3.2), U13.13 (B6)
unnamed: RN11.7 (R2.2), U13.12 (B7)
unnamed: RN11.8 (R1.2), U13.11 (B8)
unnamed: RN12.5 (R4.2), U13.20 (B1)
unnamed: RN12.6 (R3.2), U13.19 (B2)
unnamed: RN12.7 (R2.2), U13.18 (B3)
unnamed: RN12.8 (R1.2), U13.17 (B4)
unnamed: RN13.1 (R1.1), U15.20 (B1)
unnamed: RN13.2 (R2.1), U15.19 (B2)
unnamed: RN13.3 (R3.1), U15.18 (B3)
unnamed: RN13.4 (R4.1), U15.17 (B4)
unnamed: RN14.1 (R1.1), U15.14 (B5)
unnamed: RN14.2 (R2.1), U15.13 (B6)
unnamed: RN14.3 (R3.1), U15.12 (B7)
unnamed: RN14.4 (R4.1), U15.11 (B8)
unnamed: RN15.1 (R1.1), U12.20 (B1)
unnamed: RN15.2 (R2.1), U12.19 (B2)
unnamed: RN15.3 (R3.1), U12.18 (B3)
unnamed: RN15.4 (R4.1), U12.17 (B4)
unnamed: RN16.1 (R1.1), U12.14 (B5)
unnamed: RN16.2 (R2.1), U12.13 (B6)
unnamed: RN16.3 (R3.1), U12.12 (B7)
unnamed: RN16.4 (R4.1), U12.11 (B8)
unnamed: U3.8 (FB), U5.3 (P1), U5.7 (P2)
PE_DAS_MGT: J29.10 (DAS/~DSS~/~LED1), U11.N13 (IO_L23P_T3_A03_D19_14)
PE_DEVSLP_MGT: J29.38 (DEVSLP), U11.P16 (IO_L24P_T3_A01_D17_14)
PE_NCLKREQ_MGT: J29.52 (~CLKREQ), U11.N14 (IO_L23N_T3_A02_D18_14)
PE_NRST_MGT: J29.50 (~PERST), U11.R17 (IO_L24N_T3_A00_D16_14)
PE_NWAKE_MGT: J29.54 (~PEWAKE), U11.R16 (IO_L22N_T3_A04_D20_14)
PE_PEDET_MGT: J29.69 (PEDET), U11.N15 (IO_25_14)
PE_SUSCLK_MGT: J29.68 (SUSCLK), U11.P20 (IO_0_14)
VCCAUX: C12.1, C16.1, C20.1, C25.1, C30.1, C34.1, C38.1, C44.1, C65.1, C66.1, C67.1, J3.4, J4.4, J5.4, J6.4, Q1.2 (S), R41.2, U8.9 (OUT), U8.10 (OUT), U11.E12 (VCCBATT_0), U11.H12 (VCCAUX), U11.K10 (VCCADC_0), U11.K12 (VCCAUX), U11.M12 (VCCAUX), U11.P12 (VCCAUX), U11.R11 (VCCAUX), X1.1 (EN), X1.4 (Vdd)
VCCBRAM: C10.1, C14.1, C18.1, C23.1, C28.1, C32.1, C36.1, C42.1, J3.8, J4.8, J5.8, J6.8, R37.2, U6.9 (OUT), U6.10 (OUT), U11.D6 (MGTAVCC), U11.D10 (MGTAVCC), U11.E8 (MGTAVCC), U11.F7 (MGTAVCC), U11.F9 (MGTAVCC), U11.H8 (VCCINT), U11.H10 (VCCINT), U11.J7 (VCCINT), U11.J9 (VCCINT), U11.J11 (VCCBRAM), U11.K8 (VCCINT), U11.L7 (VCCINT), U11.L11 (VCCBRAM), U11.M8 (VCCINT), U11.N7 (VCCINT), U11.N11 (VCCBRAM), U11.P8 (VCCINT), U11.P10 (VCCINT), U11.R7 (VCCINT), U11.R9 (VCCINT), U11.T8 (VCCINT), U11.T10 (VCCINT)
VCCDDR_1.35V: C13.1, C17.1, C21.1, C26.1, C31.1, C35.1, C39.1, C50.1, C52.1, C69.1, C70.1, C71.1, C72.1, C73.1, C74.1, C77.1, R45.2, U9.9 (OUT), U9.10 (OUT), U10.1 (VIN), U11.AA7 (VCCO_34), U11.AB4 (VCCO_34), U11.R5 (VCCO_34), U11.T2 (VCCO_34), U11.V6 (VCCO_34), U11.W3 (VCCO_34), U17.A2 (VDD), U17.A9 (VDD), U17.B9 (VDDQ), U17.C1 (VDDQ), U17.D7 (VDD), U17.E2 (VDDQ), U17.E9 (VDDQ), U17.G2 (VDD), U17.G8 (VDD), U17.K1 (VDD), U17.K9 (VDD), U17.M1 (VDD), U17.M9 (VDD)
VCCDDR_1.35V_VREF: C48.1, C49.1, C75.1, C76.1, C77.2, C78.1, C79.2, C80.1, C82.1, R70.2, R71.1, R72.1, R73.1, R74.1, R75.1, R76.1, R77.1, R78.1, R79.1, R80.1, R81.1, R82.1, R83.1, R84.1, R85.1, R86.1, R87.1, R89.1, R90.1, R91.1, R92.1, R93.1, R94.1, R95.1, R96.1, U10.4 (VOUT), U17.E1 (VREFDQ), U17.J8 (VREFCA)
VCCFPGA_S0_PG: R33.1, U3.5 (EN), U6.3 (PG), U7.5 (EN), U8.5 (EN), U9.5 (EN)
VCCFPGA_S1_1.2V: C11.1, C15.1, C19.1, C24.1, C29.1, C33.1, C37.1, C43.1, J3.6, J4.6, J5.6, J6.6, R39.2, U7.9 (OUT), U7.10 (OUT)
VCCFPGA_S1_MGT: C40.1, R28.2, R30.2, R32.2, R48.1, U3.9 (OUT), U3.10 (OUT), U11.B5 (MGTAVTT), U11.B7 (MGTAVTT), U11.B9 (MGTAVTT), U11.B11 (MGTAVTT), U11.C4 (MGTAVTT), U11.C8 (MGTAVTT)
VCCFPGA_S1_PG: Q1.1 (G), Q2.1 (G), Q3.1 (G), Q4.1 (G), Q5.1 (G), R9.2, R13.2, R14.2, R15.2, R16.2, U4.4 (Y)
VCCFPGA_S1_VARIABLE_V1: Q2.3 (D), R19.1, U11.AA17 (VCCO_13), U11.AB14 (VCCO_13), U11.V16 (VCCO_13), U11.W13 (VCCO_13), U11.Y10 (VCCO_13)
VCCFPGA_S1_VARIABLE_V2: Q3.3 (D), R21.1, U11.A17 (VCCO_16), U11.B14 (VCCO_16), U11.C21 (VCCO_16), U11.D18 (VCCO_16), U11.E15 (VCCO_16), U11.F22 (VCCO_16)
VCCFPGA_S1_VARIABLE_V3: Q4.3 (D), R23.1, U11.G19 (VCCO_15), U11.H16 (VCCO_15), U11.J13 (VCCO_15), U11.K20 (VCCO_15), U11.L17 (VCCO_15), U11.N21 (VCCO_15)
VCCFPGA_S1_VARIABLE_V4: Q5.3 (D), R25.1, U11.C1 (VCCO_35), U11.F2 (VCCO_35), U11.H6 (VCCO_35), U11.J3 (VCCO_35), U11.M4 (VCCO_35), U11.N1 (VCCO_35)
VCCFPGA_S1_VCCO_1.8v: Q1.3 (D), R11.1, U11.R14 (IO_L19N_T3_A09_D25_VREF_14), U11.T20 (IO_L6N_T0_D08_VREF_14), U11.U22 (IO_L3P_T0_DQS_PUDC_B_14)
VCCFPGA_S1_VCCO_CONFIG: C68.2, J32.5, R10.1, R11.2, R50.1, R51.1, R57.2, R58.2, R59.2, R60.2, R62.2, R63.1, R64.1, U11.F12 (VCCO_0), U11.M14 (VCCO_14), U11.P18 (VCCO_14), U11.R15 (VCCO_14), U11.T12 (VCCO_0), U11.T22 (VCCO_14), U11.U19 (VCCO_14), U11.Y20 (VCCO_14), U12.5 (VL), U13.5 (VL), U14.5 (VL), U15.5 (VL), U16.2 (VCC), U16.3 (~RESET~/NC)
VCCFPGA_S1_VREF_V1: J7.1, J26.1, U11.Y14 (IO_L6N_T0_VREF_13)
VCCFPGA_S1_VREF_V2: J8.1, J26.2, U11.C20 (IO_L19N_T3_VREF_16), U11.D15 (IO_L6N_T0_VREF_16)
VCCFPGA_S1_VREF_V3: J9.1, J26.3, U11.H18 (IO_L6N_T0_VREF_15), U11.K14 (IO_L19N_T3_A21_VREF_15)
VCCFPGA_S1_VREF_V4: J10.1, J26.4, U11.N3 (IO_L19N_T3_VREF_35)
VTRANS_OE: R47.1, U11.T21 (IO_L4P_T0_D04_14), U12.6 (OE), U13.6 (OE), U14.6 (OE), U15.6 (OE)
sys_clk_N: U11.G3 (IO_L11N_T1_SRCC_35), U11.G4 (IO_L12N_T1_MRCC_35)

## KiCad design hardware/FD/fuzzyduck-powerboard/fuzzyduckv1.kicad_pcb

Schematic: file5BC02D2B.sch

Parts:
C1, C2, C3, C4: 200uF Electrolytic; CP_Elec_6.3x5.4_Nichicon
C70, C71, C72, C73: 10uF X7R; C_0805_2012Metric
D1, D2: LED; LED_0805_2012Metric
J1: Conn_02x12_Top_Bottom; Molex_Mini-Fit_Jr_5566-24A2_2x12_P4.20mm_Vertical
J2, J4, J5, J8, J9: Conn_01x01_Male; Banana_Jack_1Pin
J3, J6, J7, J10, J11, J20, J21, J24, J25: Conn_01x05; PinHeader_1x05_P2.54mm_Vertical
J17: Conn_01x03_Male; PinHeader_1x03_P2.54mm_Vertical
R1, R2, R3, R4: 100k; R_0805_2012Metric
R5, R6, R7, R9, R11: 10K 0.1%; R_0805_2012Metric
R8: 3.83K 0.1%; R_0805_2012Metric
R10: 7.15K 0.1%; R_0805_2012Metric
R12: 5K 0.5%; R_0805_2012Metric
R13, R14: 220; R_0805_2012Metric
R18: 5.9K 0.5%; R_0805_2012Metric
R19, R22: 120; R_0805_2012Metric
R20: 100; R_0805_2012Metric
R21: 180; R_0805_2012Metric
SW1: SW_SPDT; SW_SPDT_CK-JS102011SAQN
U2, U3, U4, U5: MIC69502

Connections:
+1.0V: C70.1, J20.1, J20.2, J20.3, J20.4, J20.5, R5.1, R20.1, U2.5, U2.6
+1.2V: C72.1, J21.1, J21.2, J21.3, J21.4, J21.5, R9.1, R19.1, U4.5, U4.6
+1.8V: C71.1, J24.1, J24.2, J24.3, J24.4, J24.5, R7.1, R21.1, U3.5, U3.6
+3.3V: J1.1, J1.2, J1.12, J1.13, J8.1, J10.1, J10.2, J10.3, J10.4, J10.5
+5V: C1.1, C2.1, C3.1, C4.1, J1.4, J1.6, J1.21, J1.22, J1.23, J5.1, J7.1, J7.2, J7.3, J7.4, J7.5, U2.2, U2.3, U3.2, U3.3, U4.2, U4.3, U5.2, U5.3
+12V: J1.10, J1.11, J2.1, J3.1, J3.2, J3.3, J3.4, J3.5
-12V: J1.14, J4.1, J6.1, J6.2, J6.3, J6.4, J6.5
ATX_POWEROK: J1.8, R1.2, R2.2, R3.2, R4.2, R14.2
GND: C1.2, C2.2, C3.2, C4.2, C70.2, C71.2, C72.2, C73.2, D1.1, D2.1, J1.3, J1.5, J1.7, J1.15, J1.17, J1.18, J1.19, J1.24, J9.1, J11.1, J11.2, J11.3, J11.4, J11.5, R6.2, R8.2, R10.2, R12.1, R18.1, R19.2, R20.2, R21.2, R22.2, SW1.3 (C), U2.4, U3.4, U4.4, U5.4
unnamed: D1.2, R13.1
unnamed: D2.2, R14.1
unnamed: J1.9, R13.2
unnamed: J1.16, SW1.2 (B)
unnamed: J17.1, R18.2
unnamed: J17.2, R11.2, U5.7
unnamed: J17.3, R12.2
unnamed: R1.1, U2.1
unnamed: R2.1, U3.1
unnamed: R3.1, U4.1
unnamed: R4.1, U5.1
unnamed: R5.2, R6.1, U2.7
unnamed: R7.2, R8.1, U3.7
unnamed: R9.2, R10.1, U4.7
VCC_DDR: C73.1, J25.1, J25.2, J25.3, J25.4, J25.5, R11.1, R22.1, U5.5, U5.6

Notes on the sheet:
Links between power rail net names
convenience connectors to ATX power rails
CONNECTORS Regulated power rails

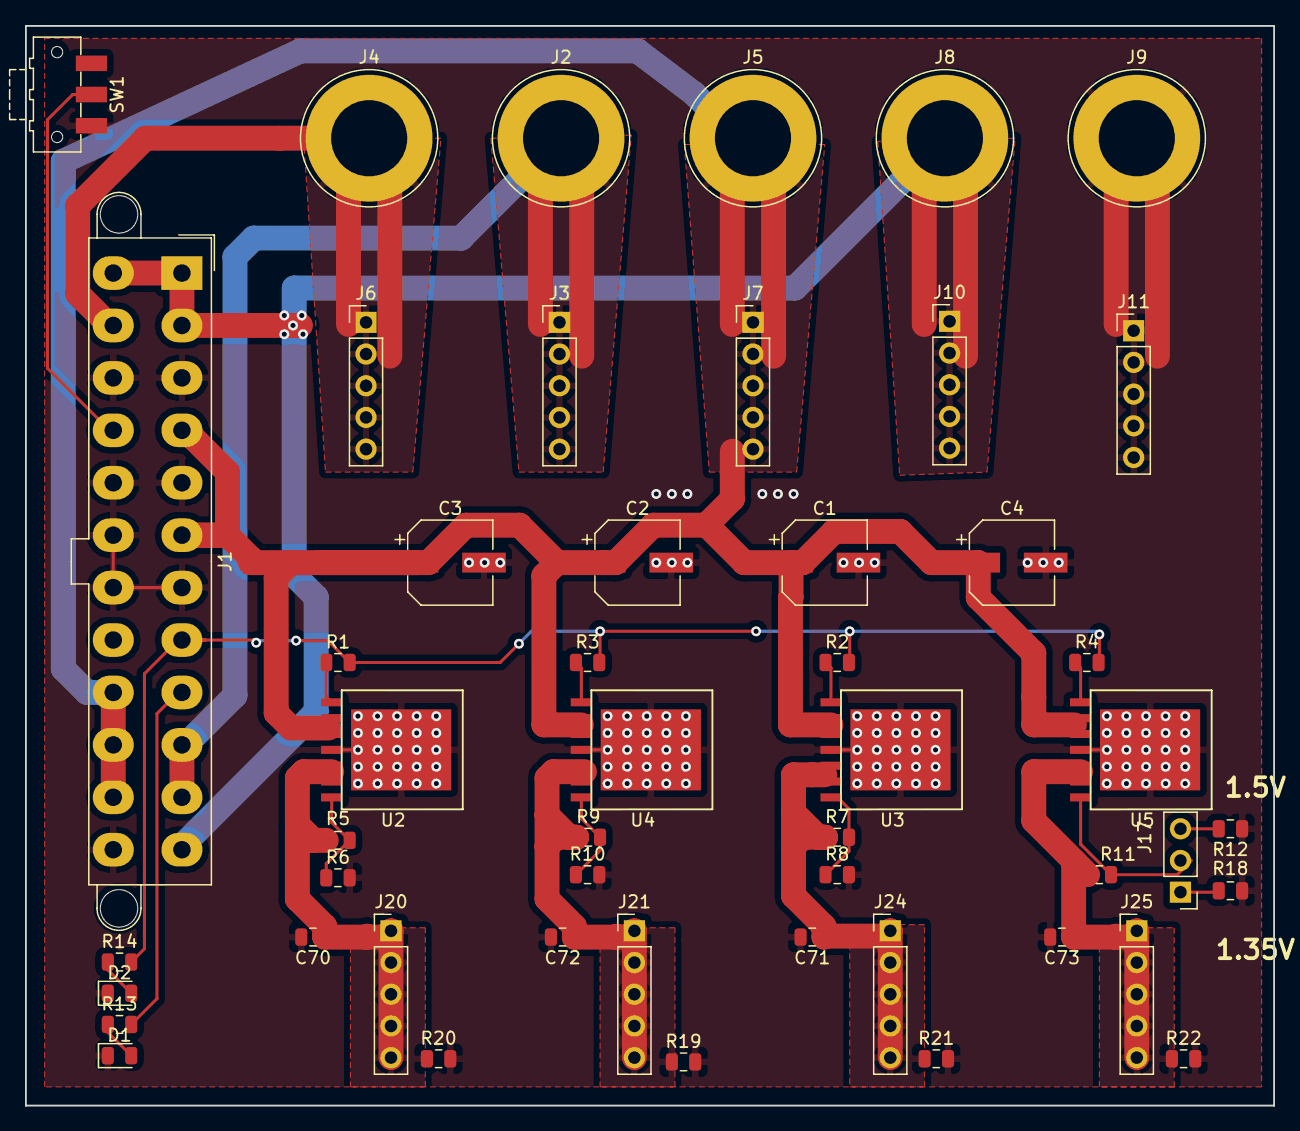
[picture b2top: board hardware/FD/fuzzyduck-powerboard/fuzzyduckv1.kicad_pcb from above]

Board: 2 copper layers, 100.0 x 86.5 mm, 50 parts (0 on the bottom side), 24 nets.
